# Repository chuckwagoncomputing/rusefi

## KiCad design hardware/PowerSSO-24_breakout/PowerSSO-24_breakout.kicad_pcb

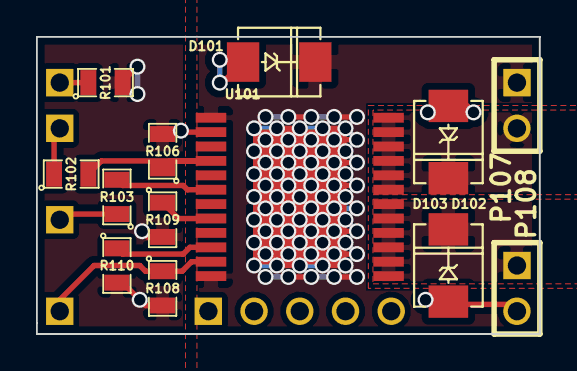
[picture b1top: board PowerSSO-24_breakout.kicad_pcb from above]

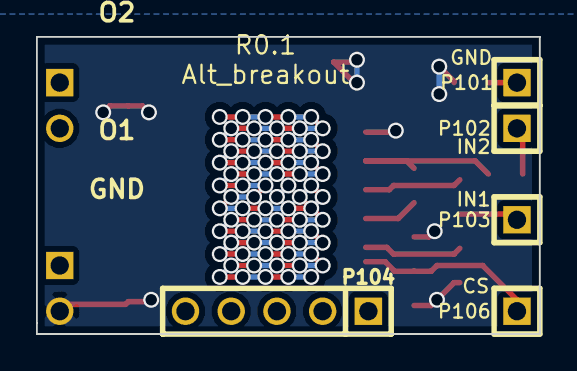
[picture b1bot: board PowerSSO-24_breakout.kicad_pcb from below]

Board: 2 copper layers, 27.9 x 16.5 mm, 18 parts (5 on the bottom side), 12 nets.

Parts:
D101, D102, D103: P6SMB36AT3G; DO-214AA(SMB)
P101, P102, P103, P106: CONN_1; SIL-1
P104: CONN_5; SIL-5
P107, P108: CONN_2; SIL-2
R101: TBD; SM0805
R102, R103, R106, R108: 10K; SM0805
R109, R110: 1K; SM0805
U101: VND5E025AKTR; PowerSSO-24

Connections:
/CS_DIS: P106.1, R108.1, U101.11
/I1: R109.1, U101.8
/I2: R110.1, U101.10
/IN1: R103.2, U101.6
/IN2: R102.2, R106.1, U101.4
/O1: D103.2, P108.1, U101.13, U101.14, U101.15, U101.16, U101.17, U101.18
/O2: D102.2, P107.2, U101.19, U101.20, U101.21, U101.22, U101.23, U101.24
/VCC: D101.2, P107.1, U101.1, U101.12, U101.EXP
GND: D101.1, D102.1, D103.1, P108.2, R101.2, R106.2, R108.2, R109.2, R110.2, U101.2
unnamed: P101.1, R101.1
unnamed: P103.1, R103.1
unnamed: P102.1, R102.1

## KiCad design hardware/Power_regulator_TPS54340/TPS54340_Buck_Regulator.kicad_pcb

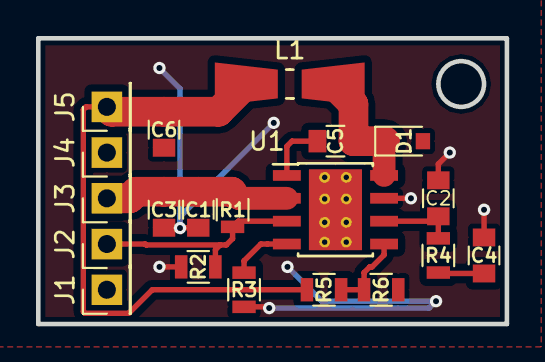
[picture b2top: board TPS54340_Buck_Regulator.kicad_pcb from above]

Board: 2 copper layers, 26.0 x 15.9 mm, 20 parts (0 on the bottom side), 10 nets.

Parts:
C1, C3: 2.2uF; C_0805
C2: 47pF; C_0805
C4: 5600pF; C_0805
C5: 0.1uF; C_0805
C6: 100uF; C_0805
D1: B560C; D_0805
J1, J2, J3, J4, J5: Conn_01x01; Pin_Header_Straight_1x01_Pitch2.54mm
L1: 5.6uH; Resistor_SMDuniversal_0805to1206_HandSoldering
R1: 365k; R_0805
R2: 86k6; R_0805
R3: 162k; R_0805
R4: 11k5; R_0805
R5: 31.6; R_0805
R6: 10.2; R_0805
U1: TPS54340; TI_SO-PowerPAD-8_ThermalVias

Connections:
/BOOT: C5.2, U1.1
/COMP: C2.1, R4.1, U1.6
/EN: J2.1, R1.1, R2.1, U1.3
/FB: R5.2, R6.1, U1.5
/RT/CLK: R3.1, U1.4
/SW: C5.1, D1.1, L1.1, U1.8
/VIN: C1.2, C3.2, J3.1, R1.2, U1.2
/VOUT: C6.1, J5.1, L1.2, R5.1
GND: C1.1, C2.2, C3.1, C4.2, C6.2, D1.2, J1.1, J4.1, R2.2, R3.2, R6.2, U1.7, U1.9
unnamed: C4.1, R4.2

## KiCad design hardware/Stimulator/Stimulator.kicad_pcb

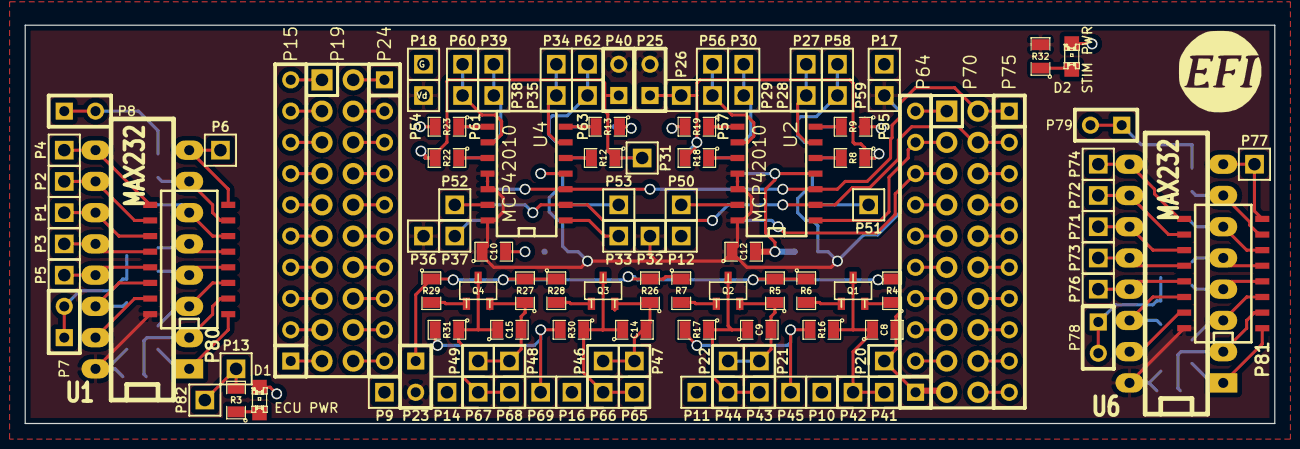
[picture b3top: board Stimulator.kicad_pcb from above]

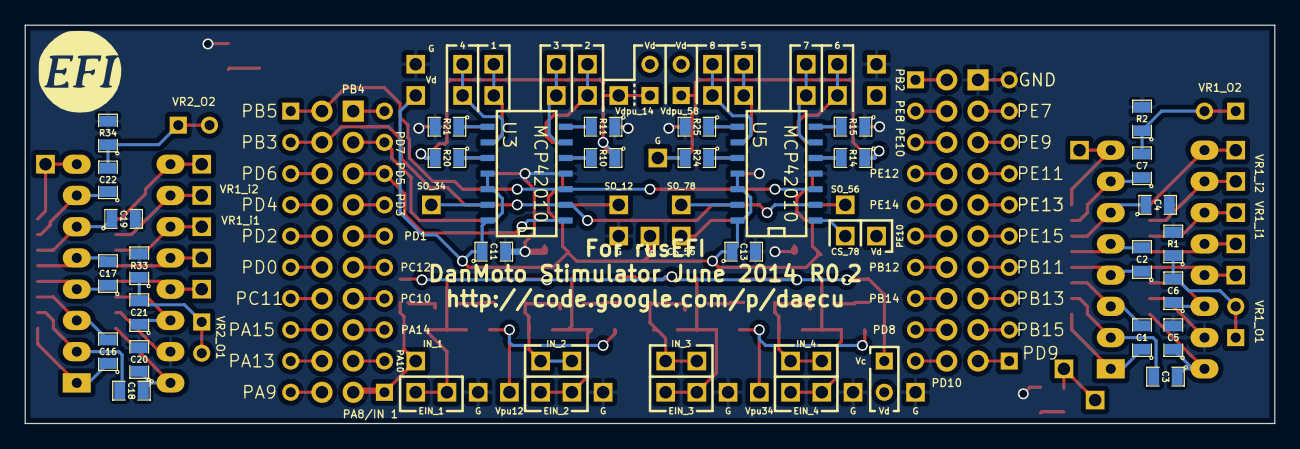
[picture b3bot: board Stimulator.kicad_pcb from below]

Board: 2 copper layers, 101.6 x 32.4 mm, 150 parts (30 on the bottom side), 122 nets.

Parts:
C1, C2, C3, C4, C5, C6, C7, C16, C17, C18, C19, C20, C21, C22: 1uF; SM0805
C8, C9, C14, C15: 100 pF; SM0805
C10, C11, C12, C13: 0.1uF; SM0805
D1: ECU PWR; LED-0805
D2: STIM PWR; LED-0805
P1, P2, P3, P4, P5, P6, P9, P10, P11, P12, P13, P14, P16, P17, P18, P20, P21, P22, P26, P27, P28, P29, P30, P31, P32, P33, P34, P35, P36, P37, P38, P39, P41, P42, P43, P44, P45, P46, P47, P48, P49, P50, P51, P52, P53, P54, P55, P56, P57, P58, P59, P60, P61, P62, P63, P65, P66, P67, P68, P69, P71, P72, P73, P74, P76, P77, P82: CONN_1; PIN_ARRAY_1
P7, P8, P23, P25, P40, P78, P79: TEST; SIL-2
P15, P24, P64, P75: CONN_10; SIL-10
P19, P70: CONN_10X2; Pin_Header_Straight_2x10
P80, P81: DIL16; SO16N
Q1, Q2, Q3, Q4: 2N7002; sot23
R1, R2, R4, R5, R6, R7, R16, R17, R26, R27, R28, R29, R30, R31, R33, R34: 10k; SM0805
R3, R32: 700R; SM0805
R8, R9, R10, R11, R12, R13, R14, R15, R18, R19, R20, R21, R22, R23, R24, R25: 0; SM0805
U1, U6: MAX232; DIP-16__300_ELL
U2, U3, U4, U5: MCP42010; SO14N

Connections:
/CS_12: P64.9, P70.3, U2.1
/CS_34: P64.8, P70.5, U3.1
/CS_56: P33.1, U4.1
/CS_78: P37.1, U5.1
/EIN_1: C8.1, P41.1, P42.1, Q1.2, R16.1
/EIN_2: C9.1, P43.1, P44.1, Q2.2, R17.1
/EIN_3: C14.1, P65.1, P66.1, Q3.2, R30.1
/EIN_4: C15.1, P67.1, P68.1, Q4.2, R31.1
/IN_1: C8.2, P20.1, P64.1, P70.19, Q1.3, R4.1
/IN_2: C9.2, P21.1, P22.1, Q2.3, R5.1
/IN_3: C14.2, P46.1, P47.1, Q3.3, R26.1
/IN_4: C15.2, P48.1, P49.1, Q4.3, R27.1
/MISO: P64.10, P70.1
/MOSI: P70.2, P75.1, U2.3, U3.3, U4.3, U5.3
/OUT1: P27.1, P28.1, U2.6
/OUT2: P56.1, P57.1, U2.9
/OUT3: P29.1, P30.1, U3.6
/OUT4: P58.1, P59.1, U3.9
/OUT5: P34.1, P35.1, U4.6
/OUT6: P60.1, P61.1, U4.9
/OUT7: P38.1, P39.1, U5.6
/OUT8: P62.1, P63.1, U5.9
/SCK: P70.4, P75.2, U2.2, U3.2, U4.2, U5.2
/U1-01: C1.1, P80.1, U1.1
/U1-02: C3.2, P80.2, U1.2
/U1-03: C1.2, P80.3, U1.3
/U1-04: C2.1, P80.4, U1.4
/U1-05: C2.2, P80.5, U1.5
/U1-06: C4.1, P80.6, U1.6
/U1-07: C7.1, P80.7, U1.7
/U1-08: P6.1, P80.8, U1.8
/U1-09: P4.1, P80.9, U1.9
/U1-12: P3.1, P80.12, U1.12
/U1-13: P5.1, P80.13, U1.13
/U1-14: C6.1, P80.14, U1.14
/U6-01: C16.1, P81.1, U6.1
/U6-02: C18.2, P81.2, U6.2
/U6-03: C16.2, P81.3, U6.3
/U6-04: C17.1, P81.4, U6.4
/U6-05: C17.2, P81.5, U6.5
/U6-06: C19.1, P81.6, U6.6
/U6-07: C22.1, P81.7, U6.7
/U6-08: P77.1, P81.8, U6.8
/U6-09: P74.1, P81.9, U6.9
/U6-12: P73.1, P81.12, U6.12
/U6-13: P76.1, P81.13, U6.13
/U6-14: C21.1, P81.14, U6.14
/VR1-O1: C6.2, P7.1, P7.2, R1.1
/VR1-O2: C7.2, P8.1, P8.2, R2.1
/VR1_i1: P1.1, P80.11, U1.11
/VR1_i2: P2.1, P80.10, U1.10
/VR2-O1: C21.2, P78.1, P78.2, R33.1
/VR2-O2: C22.2, P79.1, P79.2, R34.1
/VR2_i1: P71.1, P81.11, U6.11
/VR2_i2: P72.1, P81.10, U6.10
/Vc: P23.1, R4.2, R5.2, R6.1, R7.1, R26.2, R27.2, R28.1, R29.1
/Vd: C3.1, C5.1, C10.1, C11.1, C12.1, C13.1, C18.1, C20.1, P23.2, P25.2, P32.1, P36.1, P40.2, P54.1, P55.1, P80.16, P81.16, R32.2, U1.16, U2.11, U2.12, U2.14, U3.11, U3.12, U3.14, U4.11, U4.12, U4.14, U5.11, U5.12, U5.14, U6.16
/Vdpu_14: P25.1, P26.1, R8.1, R10.1, R18.2, R20.2
/Vdpu_58: P31.1, P40.1, R12.1, R14.1, R22.2, R24.2
/Vipu12: P45.1, R16.2, R17.2
/Vipu34: P69.1, R30.2, R31.2
GND: C4.2, C5.2, C10.2, C11.2, C12.2, C13.2, C19.2, C20.2, D1.2, D2.2, P9.1, P10.1, P11.1, P12.1, P14.1, P15.10, P16.1, P17.1, P18.1, P19.1, P80.15, P81.15, R1.2, R2.2, R9.1, R11.1, R13.1, R15.1, R19.2, R21.2, R23.2, R25.2, R33.2, R34.2, U1.15, U2.4, U3.4, U4.4, U5.4, U6.15
unnamed: P70.6, P75.3
unnamed: P70.20, P75.10
unnamed: P64.2, P70.17
unnamed: P64.3, P70.15
unnamed: P64.4, P70.13
unnamed: P64.5, P70.11
unnamed: P64.6, P70.9
unnamed: P64.7, P70.7
unnamed: P70.18, P75.9
unnamed: P70.8, P75.4
unnamed: P70.10, P75.5
unnamed: P70.12, P75.6
unnamed: P70.14, P75.7
unnamed: P70.16, P75.8
unnamed: P15.5, P19.11
unnamed: P19.4, P24.2
unnamed: P19.6, P24.3
unnamed: P19.8, P24.4
unnamed: P19.10, P24.5
unnamed: P19.12, P24.6
unnamed: P19.14, P24.7
unnamed: P19.16, P24.8
unnamed: P19.18, P24.9
unnamed: P19.20, P24.10
unnamed: P15.1, P19.19
unnamed: P15.2, P19.17
unnamed: P15.3, P19.15
unnamed: P15.4, P19.13
unnamed: P15.6, P19.9
unnamed: P15.7, P19.7
unnamed: P15.8, P19.5
unnamed: P15.9, P19.3
unnamed: P19.2, P24.1
unnamed: R14.2, U5.5
unnamed: R15.2, U5.7
unnamed: R25.1, U5.8
unnamed: R24.1, U5.10
unnamed: P50.1, U2.13
unnamed: P52.1, U4.13
unnamed: P51.1, U3.13
unnamed: P53.1, U5.13
unnamed: P13.1, P82.1, R3.2
unnamed: D2.1, R32.1
unnamed: D1.1, R3.1
unnamed: R8.2, U2.5
unnamed: R9.2, U2.7
unnamed: R19.1, U2.8
unnamed: R18.1, U2.10
unnamed: R10.2, U3.5
unnamed: Q3.1, R28.2
unnamed: Q2.1, R7.2
unnamed: Q4.1, R29.2
unnamed: R11.2, U3.7
unnamed: R21.1, U3.8
unnamed: R20.1, U3.10
unnamed: R12.2, U4.5
unnamed: R13.2, U4.7
unnamed: R23.1, U4.8
unnamed: R22.1, U4.10
unnamed: Q1.1, R6.2

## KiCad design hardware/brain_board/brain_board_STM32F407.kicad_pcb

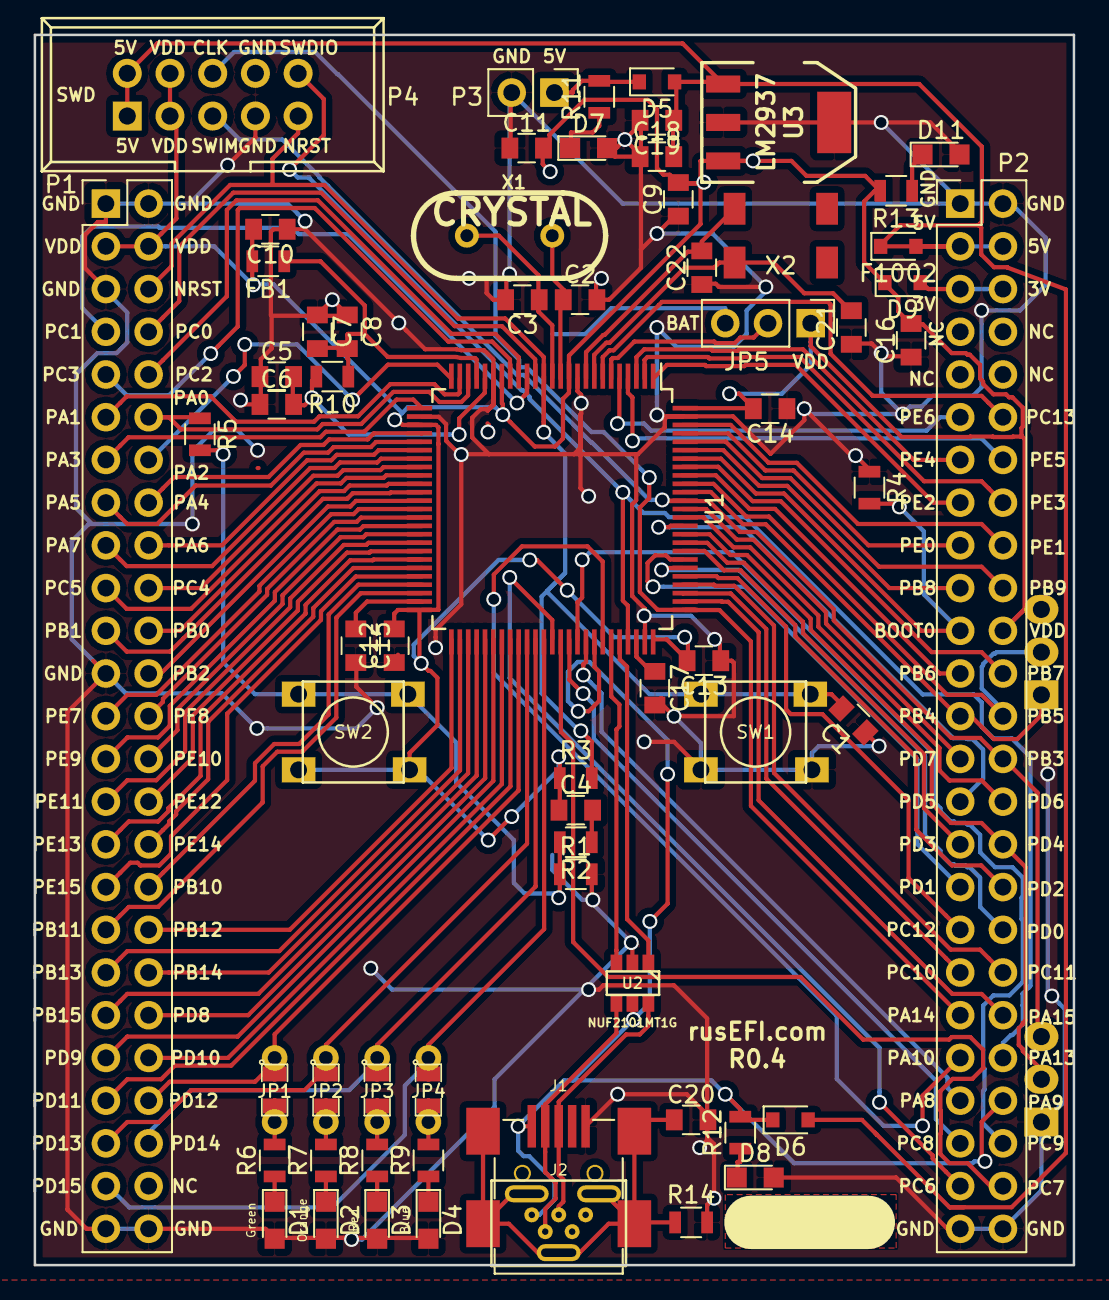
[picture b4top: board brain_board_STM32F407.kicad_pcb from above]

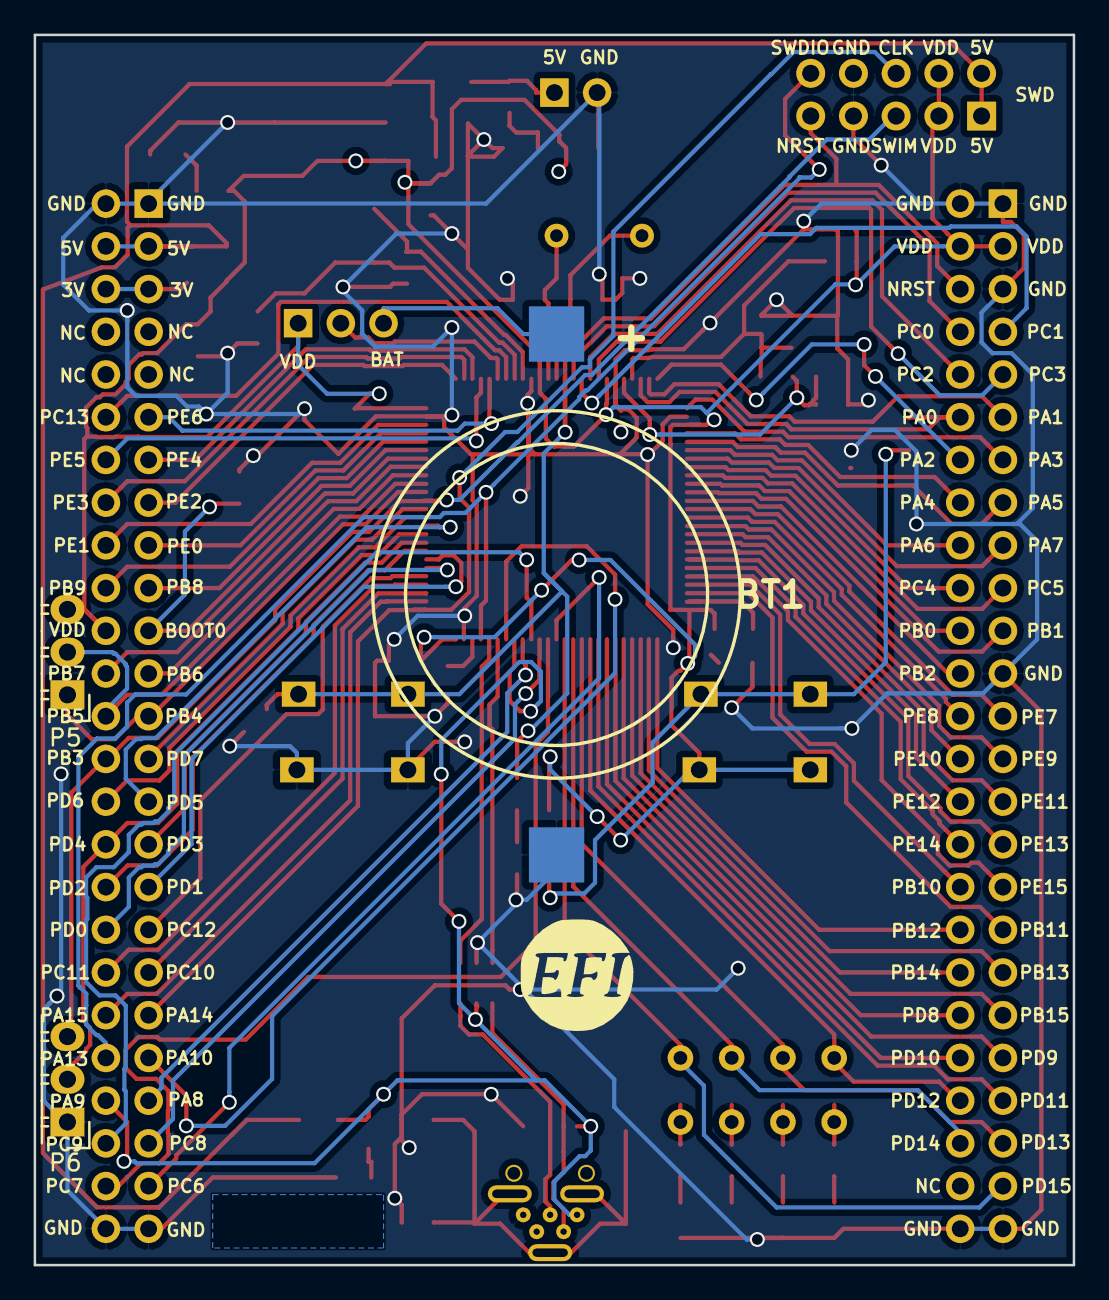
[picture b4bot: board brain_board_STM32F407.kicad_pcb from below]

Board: 2 copper layers, 61.8 x 73.2 mm, 70 parts (4 on the bottom side), 111 nets.

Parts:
BT1: BATTERY_CR2032; BATT_CR2032_MPD
C1: 20nF; C_0805
C2, C3, C21, C22: 18pF; C_0805
C4, C15, C17: 2u2F; C_0805
C5, C8: 0.01uF; C_0805
C6, C7, C16: 1uF; C_0805
C9, C10, C11, C12, C13, C14, C18, C20: 0.1uF; C_0805
C19: 4.7uF; C_0805
D1, D2, D3, D4, D7, D8, D11: BLUE_LED_0805; LED_0805
D5, D6, D9: PMEG2010EA; D_0805
F1002: FUSE; D_0805
FB1: FILTER; R_0805
G1: LOGO; LOGO_F
J1: MINI-USB-5P-3400020P1
J2: MINI-USB-5P-3400020P1V; MINI-USB_RCTP_V-T_B
JP1, JP2, JP3, JP4: JUMPER; SM0805_jumper
JP5: JUMPER3; Pin_Header_Straight_1x03_Pitch2.54mm
P1, P2: CONN_25X2; Pin_Header_Straight_2x25_Pitch2.54mm
P3: CONN_2; Pin_Header_Straight_1x02_Pitch2.54mm
P4: CONN_02X05; IDC_Header_Straight_10pins
P5, P6: CONN_01X03; Pin_Header_Angled_1x03
R1, R3, R4: 10k; R_0805
R2: 100R; R_0805
R5: 330R; R_0805
R6, R7, R8, R9: 680R; R_0805
R10: 47R; R_0805
R11, R12, R13: 1k; R_0805
R14: 100k; R_0805
SW1, SW2: SW_PUSH; TL-1105
U1: STM32F407VG; LQFP-100_14x14mm_Pitch0.5mm
U2: NUF2101MT1G; SOT-457
U3: LM2937; SOT223
X1: CRYSTAL; HC-49V
X2: CRYSTAL(MC306); MC-306

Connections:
/3V: D9.2, P2.5, P2.6
/5V: C18.2, C19.1, D5.2, D6.2, F1002.1, F1002.2, P2.3, P2.4, P4.1, P4.2, U3.1
/BOOT0: P2.21, R4.2, U1.94
/D+: J1.3, J2.3, U2.6
/D-: J1.2, J2.2, U2.4
/NRST: C1.2, P1.6, P4.9, R3.2, SW1.1, U1.14
/PA0: P1.12, R5.1, U1.23
/PA1: P1.11, U1.24
/PA2: P1.14, U1.25
/PA3: P1.13, U1.26
/PA4: P1.16, U1.29
/PA5: P1.15, U1.30
/PA6: P1.18, U1.31
/PA7: P1.17, U1.32
/PA8: P2.43, U1.67
/PA9: D6.1, J1.1, J2.1, P2.44, R12.2, U1.68, U2.5
/PA10: P2.41, U1.69
/PA11: U1.70, U2.3
/PA12: U1.71, U2.1
/PA13: P2.42, P4.10, U1.72
/PA14: P2.39, P4.6, U1.76
/PA15: P2.40, U1.77
/PB0: P1.22, U1.35
/PB1: P1.21, U1.36
/PB2: P1.24, U1.37
/PB3: P2.28, P4.5, P6.3, U1.89
/PB4: P2.25, P5.1, U1.90
/PB5: P2.26, P5.2, U1.91
/PB6: P2.23, U1.92
/PB7: P2.24, U1.93
/PB8: P2.19, U1.95
/PB9: P2.20, U1.96
/PB10: P1.34, U1.47
/PB11: P1.35, U1.48
/PB12: P1.36, U1.51
/PB13: P1.37, U1.52
/PB14: P1.38, U1.53
/PB15: P1.39, U1.54
/PC0: P1.8, U1.15
/PC1: P1.7, U1.16
/PC2: P1.10, U1.17
/PC3: P1.9, U1.18
/PC4: P1.20, U1.33
/PC5: P1.19, U1.34
/PC6: P2.47, U1.63
/PC7: P2.48, U1.64
/PC8: P2.45, U1.65
/PC9: P2.46, U1.66
/PC10: P2.37, U1.78
/PC11: P2.38, U1.79
/PC12: P2.35, U1.80
/PC13: P2.12, U1.7
/PD0: P2.36, U1.81
/PD1: P2.33, U1.82
/PD2: P2.34, U1.83
/PD3: P2.31, U1.84
/PD4: P2.32, P6.2, U1.85
/PD5: P2.29, U1.86
/PD6: P2.30, U1.87
/PD7: P2.27, U1.88
/PD8: P1.40, U1.55
/PD9: P1.41, U1.56
/PD10: P1.42, U1.57
/PD11: P1.43, U1.58
/PD12: JP1.1, P1.44, U1.59
/PD13: JP2.1, P1.45, U1.60
/PD14: JP3.1, P1.46, U1.61
/PD15: JP4.1, P1.47, U1.62
/PE0: P2.17, U1.97
/PE1: P2.18, U1.98
/PE2: P2.15, U1.1
/PE3: P2.16, U1.2
/PE4: P2.13, U1.3
/PE5: P2.14, U1.4
/PE6: P2.11, U1.5
/PE7: P1.25, U1.38
/PE8: P1.26, U1.39
/PE9: P1.27, U1.40
/PE10: P1.28, U1.41
/PE11: P1.29, U1.42
/PE12: P1.30, U1.43
/PE13: P1.31, U1.44
/PE14: P1.32, U1.45
/PE15: P1.33, U1.46
/Shield: C20.1, J1.6, J2.6, R14.1
/VDD: C4.1, C9.2, C10.2, C11.2, C12.2, C13.2, C14.2, C16.2, D9.1, FB1.2, JP5.1, P1.3, P1.4, P2.22, P4.3, P4.4, P5.3, R3.1, R13.2, SW2.2, U1.11, U1.19, U1.28, U1.50, U1.75, U1.100, U3.3
GND: BT1.2, C1.1, C2.2, C3.2, C5.1, C6.1, C7.1, C8.1, C9.1, C10.1, C11.1, C12.1, C13.1, C14.1, C15.2, C16.1, C17.2, C18.1, C19.2, C20.2, C21.1, C22.1, D1.2, D2.2, D3.2, D4.2, D7.2, D8.2, D11.2, J1.5, J2.5, P1.1, P1.2, P1.5, P1.23, P1.49, P1.50, P2.1, P2.2, P2.49, P2.50, P3.2, P4.7, P4.8, P6.1, R1.2, R4.1, R14.2, SW1.2, U1.10, U1.20, U1.27, U1.74, U1.99, U2.2, U3.2, U3.4
unnamed: BT1.1, JP5.3
unnamed: C2.1, U1.12, X1.2
unnamed: C3.1, U1.13, X1.1
unnamed: C4.2, R2.1
unnamed: C5.2, C6.2, R10.2, U1.21
unnamed: C7.2, C8.2, FB1.1, R10.1, U1.22
unnamed: C15.1, U1.49
unnamed: C17.1, U1.73
unnamed: C21.2, U1.8, X2.1
unnamed: C22.2, U1.9, X2.4
unnamed: D1.1, R6.1
unnamed: D2.1, R7.1
unnamed: D3.1, R8.1
unnamed: D4.1, R9.1
unnamed: D5.1, P3.1, R11.2
unnamed: D7.1, R11.1
unnamed: D8.1, R12.1
unnamed: D11.1, R13.1
unnamed: JP1.2, R6.2
unnamed: JP2.2, R7.2
unnamed: JP3.2, R8.2
unnamed: JP4.2, R9.2
unnamed: JP5.2, U1.6
unnamed: R1.1, R2.2, R5.2, SW2.1

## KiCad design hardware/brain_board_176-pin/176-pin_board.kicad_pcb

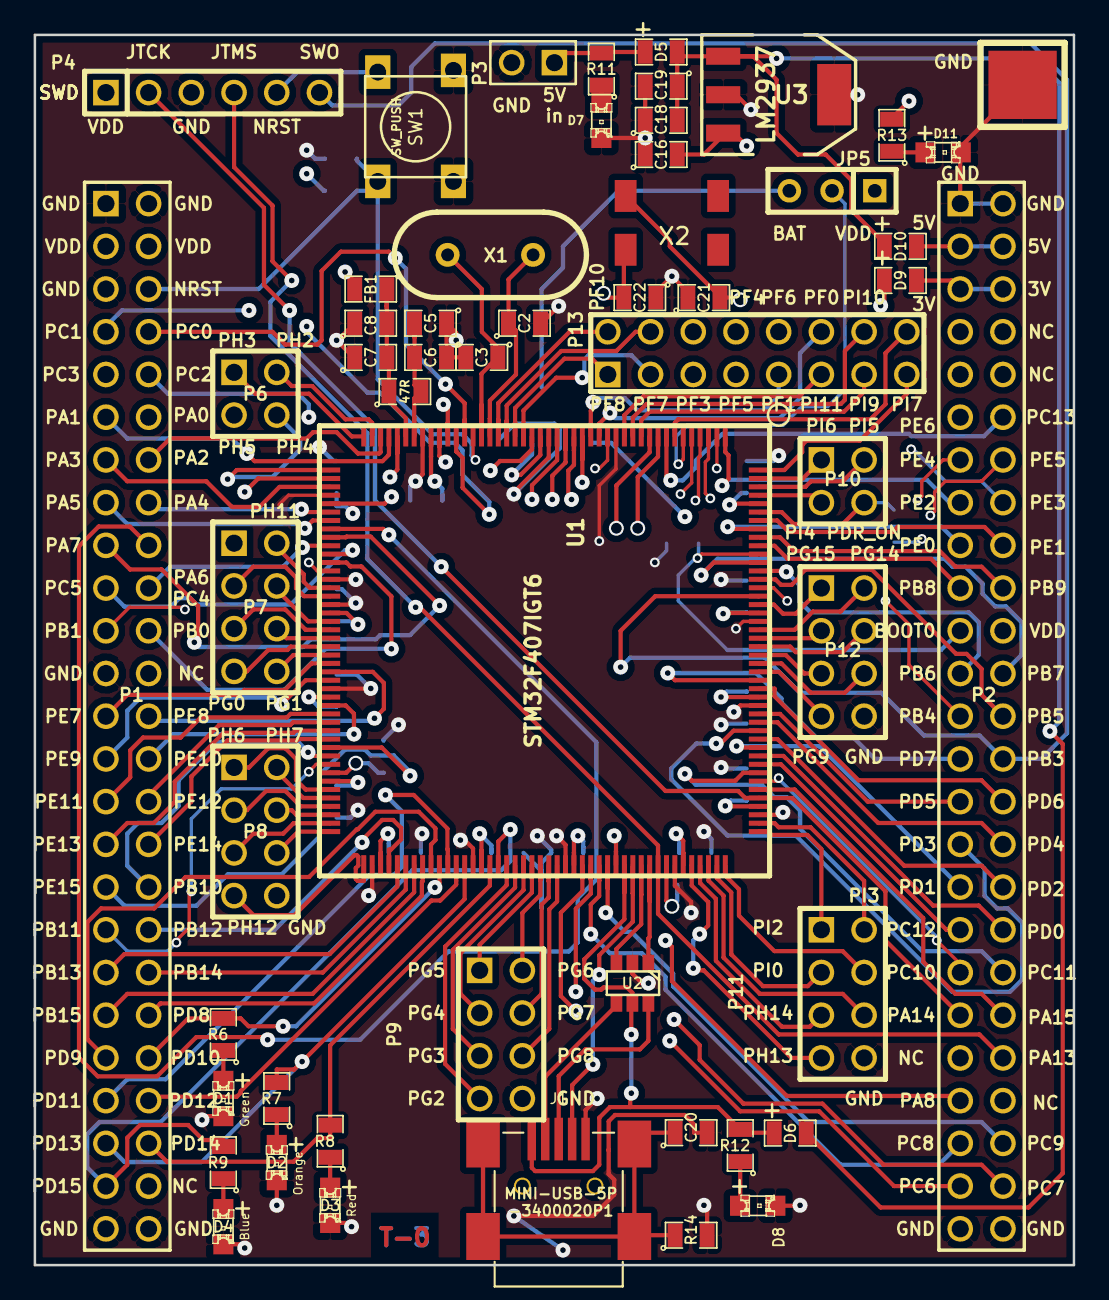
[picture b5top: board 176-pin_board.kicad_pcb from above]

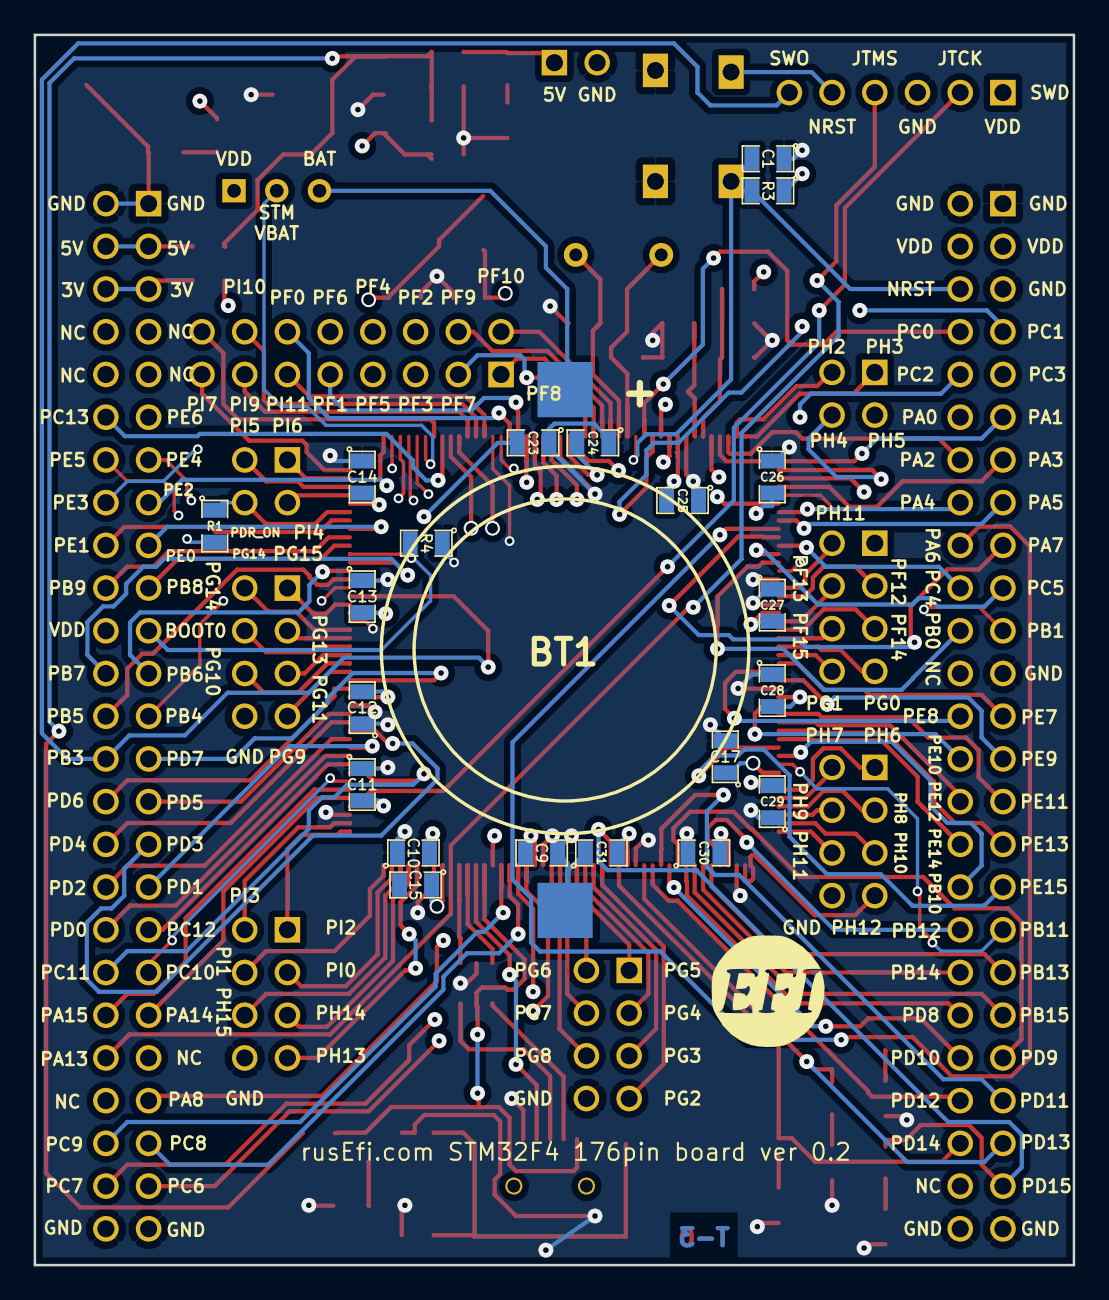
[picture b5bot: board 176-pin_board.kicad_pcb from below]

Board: 4 copper layers, 61.8 x 73.2 mm, 77 parts (23 on the bottom side), 164 nets.

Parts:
BT1: BATTERY_CR2032; BATT_CR2032_MPD
C1: 0.02uF; SM0805
C2, C3, C21, C22: 18pF; SM0805
C5, C8: 0.01uF; SM0805
C6, C7, C16: 1uF; SM0805
C9, C10, C11, C12, C13, C14, C18, C20, C23, C24, C25, C26, C27, C28, C29, C30, C31: 0.1uF; SM0805
C15, C17: 2u2F; SM0805
C19: 4.7uF; SM0805
D1, D2, D3, D4, D7, D8, D11: LED_0805; LED-0805_A
D5, D6, D9, D10: DIODESCH; SM0805-diode
FB1: FILTER; SM0805
G1: LOGO; LOGO_F
J1: MINI-USB-5P-3400020P1
JP5: JUMPER3; SIL-3
P1, P2: CONN_25X2; PIN_ARRAY_25x2_A
P3: CONN_2; PIN_ARRAY_2_A
P4: CONN_6; PIN_ARRAY-6X1
P5: CONN_1; 1PIN_SMD
P6, P10: CONN_2X2; PIN_ARRAY_2X2
P7, P8, P9, P11, P12: CONN_4X2; pin_array_4x2
P13: CONN_8X2; pin_array_8x2
R1, R11, R12, R13: 1k; SM0805
R3, R4: 10k; SM0805
R6, R7, R8, R9: 680R; SM0805
R10: 47R; SM0805
R14: 100k; SM0805
SW1: SW_PUSH; TL-1105
U1: STM32F407IGT6; LQFP-176
U2: NUF2101MT1G; SOT-457
U3: LM2937; SOT223
X1: CRYSTAL; HC-49V
X2: CRYSTAL(MC306); MC-306

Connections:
/3.3V: D9.2, P2.5, P2.6
/5V: D10.2, P2.3, P2.4
/5Vi: C18.2, C19.1, D5.2, D6.2, D10.1, U3.1
/BOOT0: P2.21, R4.2, U1.166
/D+: J1.3, U2.6
/D-: J1.2, U2.4
/NRST: C1.2, P1.6, P4.5, R3.2, SW1.1, U1.31
/PA0: P1.12, U1.40
/PA1: P1.11, U1.41
/PA2: P1.14, U1.42
/PA3: P1.13, U1.47
/PA4: P1.16, U1.50
/PA5: P1.15, U1.51
/PA6: P1.18, U1.52
/PA7: P1.17, U1.53
/PA8: P2.43, U1.119
/PA9: D6.1, J1.1, R12.2, U1.120, U2.5
/PA10: J1.4, U1.121
/PA11: U1.122, U2.3
/PA12: U1.123, U2.1
/PA13: P2.42, P4.4, U1.124
/PA14: P2.39, P4.2, U1.137
/PA15: P2.40, U1.138
/PB0: P1.22, U1.56
/PB1: P1.21, U1.57
/PB3: P2.28, P4.6, U1.161
/PB4: P2.25, U1.162
/PB5: P2.26, U1.163
/PB6: P2.23, U1.164
/PB7: P2.24, U1.165
/PB8: P2.19, U1.167
/PB9: P2.20, U1.168
/PB10: P1.34, U1.79
/PB11: P1.35, U1.80
/PB12: P1.36, U1.92
/PB13: P1.37, U1.93
/PB14: P1.38, U1.94
/PB15: P1.39, U1.95
/PC0: P1.8, U1.32
/PC1: P1.7, U1.33
/PC2: P1.10, U1.34
/PC3: P1.9, U1.35
/PC4: P1.20, U1.54
/PC5: P1.19, U1.55
/PC6: P2.47, U1.115
/PC7: P2.48, U1.116
/PC8: P2.45, U1.117
/PC9: P2.46, U1.118
/PC10: P2.37, U1.139
/PC11: P2.38, U1.140
/PC12: P2.35, U1.141
/PC13: P2.12, U1.8
/PD0: P2.36, U1.142
/PD1: P2.33, U1.143
/PD2: P2.34, U1.144
/PD3: P2.31, U1.145
/PD4: P2.32, U1.146
/PD5: P2.29, U1.147
/PD6: P2.30, U1.150
/PD7: P2.27, U1.151
/PD8: P1.40, U1.96
/PD9: P1.41, U1.97
/PD10: P1.42, R6.2, U1.98
/PD11: P1.43, U1.99
/PD12: P1.44, U1.100
/PD13: P1.45, R7.2, U1.101
/PD14: P1.46, R8.2, U1.104
/PD15: P1.47, R9.2, U1.105
/PDR_ON: P10.4, R1.1, U1.171
/PE0: P2.17, U1.169
/PE1: P2.18, U1.170
/PE2: P2.15, U1.1
/PE3: P2.16, U1.2
/PE4: P2.13, U1.3
/PE5: P2.14, U1.4
/PE6: P2.11, U1.5
/PE7: P1.25, U1.68
/PE8: P1.26, U1.69
/PE9: P1.27, U1.70
/PE10: P1.28, U1.73
/PE11: P1.29, U1.74
/PE12: P1.30, U1.75
/PE13: P1.31, U1.76
/PE14: P1.32, U1.77
/PE15: P1.33, U1.78
/PF0: P13.12, U1.16
/PF1: P13.9, U1.17
/PF2: P13.6, U1.18
/PF3: P13.5, U1.19
/PF4: P13.8, U1.20
/PF5: P13.7, U1.21
/PF6: P13.10, U1.24
/PF7: P13.3, U1.25
/PF8: P13.1, U1.26
/PF9: P13.4, U1.27
/PF10: P13.2, U1.28
/PF11: P7.2, U1.59
/PF12: P7.3, U1.60
/PF13: P7.4, U1.63
/PF14: P7.5, U1.64
/PF15: P7.6, U1.65
/PG0: P7.7, U1.66
/PG1: P7.8, U1.67
/PG2: P9.7, U1.106
/PG3: P9.5, U1.107
/PG4: P9.3, U1.108
/PG5: P9.1, U1.109
/PG6: P9.2, U1.110
/PG7: P9.4, U1.111
/PG8: P9.6, U1.112
/PG9: P12.7, U1.152
/PG10: P12.6, U1.153
/PG11: P12.5, U1.154
/PG12: P12.4, U1.155
/PG13: P12.3, U1.156
/PG14: P12.2, U1.157
/PG15: P12.1, U1.160
/PH0: C2.1, U1.29, X1.2
/PH1: C3.1, U1.30, X1.1
/PH2: P6.2, U1.43
/PH3: P6.1, U1.44
/PH4: P6.4, U1.45
/PH5: P6.3, U1.46
/PH6: P8.1, U1.83
/PH7: P8.2, U1.84
/PH8: P8.3, U1.85
/PH9: P8.4, U1.86
/PH10: P8.5, U1.87
/PH11: P8.6, U1.88
/PH12: P8.7, U1.89
/PH13: P11.7, U1.128
/PH14: P11.5, U1.129
/PH15: P11.6, U1.130
/PI0: P11.3, U1.131
/PI1: P11.4, U1.132
/PI2: P11.1, U1.133
/PI3: P11.2, U1.134
/PI4: P10.3, U1.173
/PI5: P10.2, U1.174
/PI6: P10.1, U1.175
/PI7: P13.15, U1.176
/PI8: P13.16, U1.7
/PI9: P13.13, U1.11
/PI10: P13.14, U1.12
/PI11: P13.11, U1.13
/VBAT: JP5.2, U1.6
/VDD: C9.2, C10.2, C11.2, C12.2, C13.2, C14.2, C16.2, C23.2, C24.2, C25.2, C26.2, C27.2, C28.2, C29.2, C30.2, C31.2, D9.1, FB1.2, JP5.1, P1.3, P1.4, P2.22, P4.1, R1.2, R3.1, R13.2, U1.15, U1.23, U1.36, U1.49, U1.62, U1.72, U1.82, U1.91, U1.103, U1.114, U1.127, U1.136, U1.149, U1.159, U1.172, U3.3
GND: BT1.2, C1.1, C2.2, C3.2, C5.1, C6.1, C7.1, C8.1, C9.1, C10.1, C11.1, C12.1, C13.1, C14.1, C15.2, C16.1, C17.2, C18.1, C19.2, C20.2, C21.1, C22.1, C23.1, C24.1, C25.1, C26.1, C27.1, C28.1, C29.1, C30.1, C31.1, D1.2, D2.2, D3.2, D4.2, D7.2, D8.2, D11.2, J1.5, P1.1, P1.2, P1.5, P1.23, P1.49, P1.50, P2.1, P2.2, P2.49, P2.50, P3.2, P4.3, P5.1, P8.8, P9.8, P11.8, P12.8, R4.1, R14.2, SW1.2, U1.14, U1.22, U1.37, U1.48, U1.58, U1.61, U1.71, U1.90, U1.102, U1.113, U1.126, U1.135, U1.148, U1.158, U2.2, U3.2, U3.4
unnamed: C7.2, C8.2, FB1.1, R10.1, U1.39
unnamed: D11.1, R13.1
unnamed: D2.1, R7.1
unnamed: D1.1, R6.1
unnamed: C5.2, C6.2, R10.2, U1.38
unnamed: D3.1, R8.1
unnamed: D5.1, P3.1, R11.2
unnamed: BT1.1, JP5.3
unnamed: D4.1, R9.1
unnamed: D7.1, R11.1
unnamed: D8.1, R12.1
unnamed: C20.1, J1.6, R14.1
unnamed: C21.2, U1.9, X2.4
unnamed: C22.2, U1.10, X2.1
unnamed: C15.1, U1.125
unnamed: C17.1, U1.81

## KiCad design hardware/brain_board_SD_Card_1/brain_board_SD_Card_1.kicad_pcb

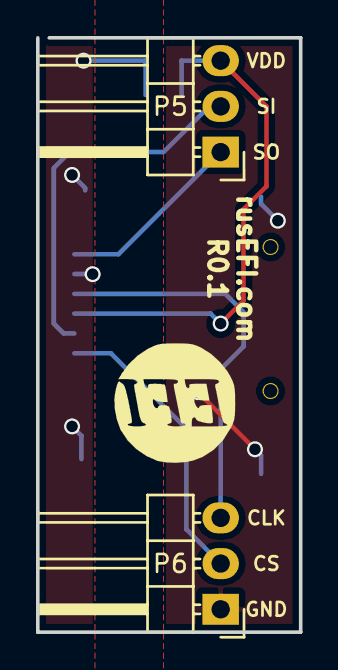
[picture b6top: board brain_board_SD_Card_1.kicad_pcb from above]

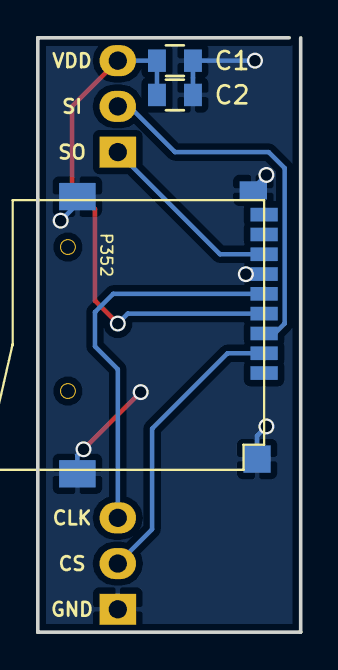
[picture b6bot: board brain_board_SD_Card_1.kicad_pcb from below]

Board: 2 copper layers, 14.6 x 33.0 mm, 6 parts (3 on the bottom side), 6 nets.

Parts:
C1: 1000pF; C_0805
C2: 0.1uF; C_0805
G1: LOGO; LOGO_F
P5, P6: CONN_01X03; Pin_Header_Angled_1x03
P352: MICRO-SDCARD-CONNECTOR-3300060P1

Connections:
/3.3V: C1.2, C2.2, P5.3, P352.4
/CS_SD_MODULE: P6.2, P352.2
/SPI_MISO: P5.1, P352.7
/SPI_MOSI: P5.2, P352.3
/SPI_SCK: P6.3, P352.5
GND: C1.1, C2.1, P6.1, P352.6, P352.G1, P352.G2, P352.G3, P352.G4

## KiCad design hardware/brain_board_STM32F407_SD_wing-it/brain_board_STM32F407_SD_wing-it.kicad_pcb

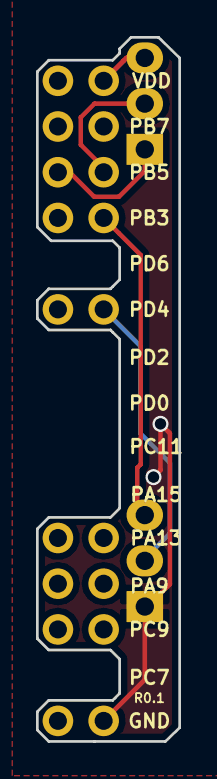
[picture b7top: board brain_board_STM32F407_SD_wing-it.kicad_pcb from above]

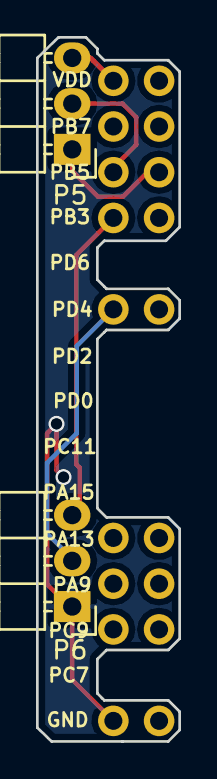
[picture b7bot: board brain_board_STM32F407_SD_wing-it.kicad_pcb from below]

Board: 2 copper layers, 7.9 x 39.1 mm, 8 parts (2 on the bottom side), 6 nets.

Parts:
P1: CONN_02X04; Pin_Header_Straight_2x04_Pitch2.54mm
P2: CONN_02X03; Pin_Header_Straight_2x03_Pitch2.54mm
P5, P6: CONN_01X03; Pin_Header_Angled_1x03
P7, P8, P11, P12: CONN_01X01; Pin_Header_Straight_1x01_Pitch2.54mm

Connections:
/PB3: P1.8, P6.3
/PB4: P1.5, P5.1
/PB5: P1.6, P5.2
/PD4: P6.2, P7.1
/VDD: P1.2, P5.3
GND: P6.1, P8.1

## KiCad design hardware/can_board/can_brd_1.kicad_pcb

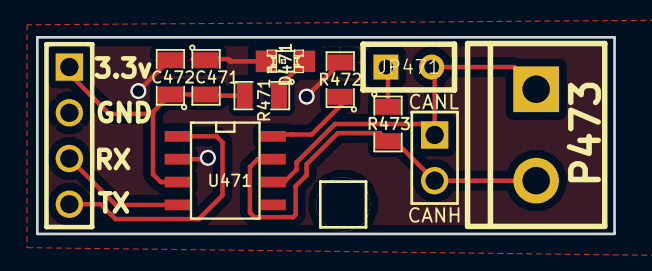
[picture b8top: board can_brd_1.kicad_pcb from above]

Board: 2 copper layers, 32.1 x 10.9 mm, 13 parts (1 on the bottom side), 9 nets.

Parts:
C471: .1uF; SM0805
C472: 4.7uF; SM0805
D471: RED; LED-0805_A
G471: LOGO; LOGO_F
JP471: JUMPER; JUMPER-2
M471: CONN_1; PIN_ARRAY_1
P471: CONN_4; PIN_ARRAY_4x1
P472: CONN_2; PIN_ARRAY_2_A
P473: CONN_2; bornier2
R471: 1k; SM0805
R472: 10k; SM0805
R473: 120; SM0805
U471: SN65HVD230; SO8E

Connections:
/3.3V: C471.2, C472.1, P471.1, R471.2, U471.3
/CANH: P472.2, P473.2, R473.2, U471.7
/CANL: JP471.2, P472.1, P473.1, U471.6
/CAN_RX: P471.3, U471.4
/CAN_TX: P471.4, U471.1
GND: C471.1, C472.2, D471.2, P471.2, R472.2, U471.2
unnamed: D471.1, R471.1
unnamed: JP471.1, R473.1
unnamed: R472.1, U471.8
